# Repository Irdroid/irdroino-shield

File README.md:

# Irdroino-shield

Irdroino shield is a prototyping shield for Arduino Like boards such as Maple, Pinguino, Olimexino and Arduino

  - Stackable headers
- Two buttons
- One LED
- Prototype Area PTH 
- SMD IC Area
- IR Receiver IC (OSRB38C9BA)
- One Infrared LED (L-53F3BT)

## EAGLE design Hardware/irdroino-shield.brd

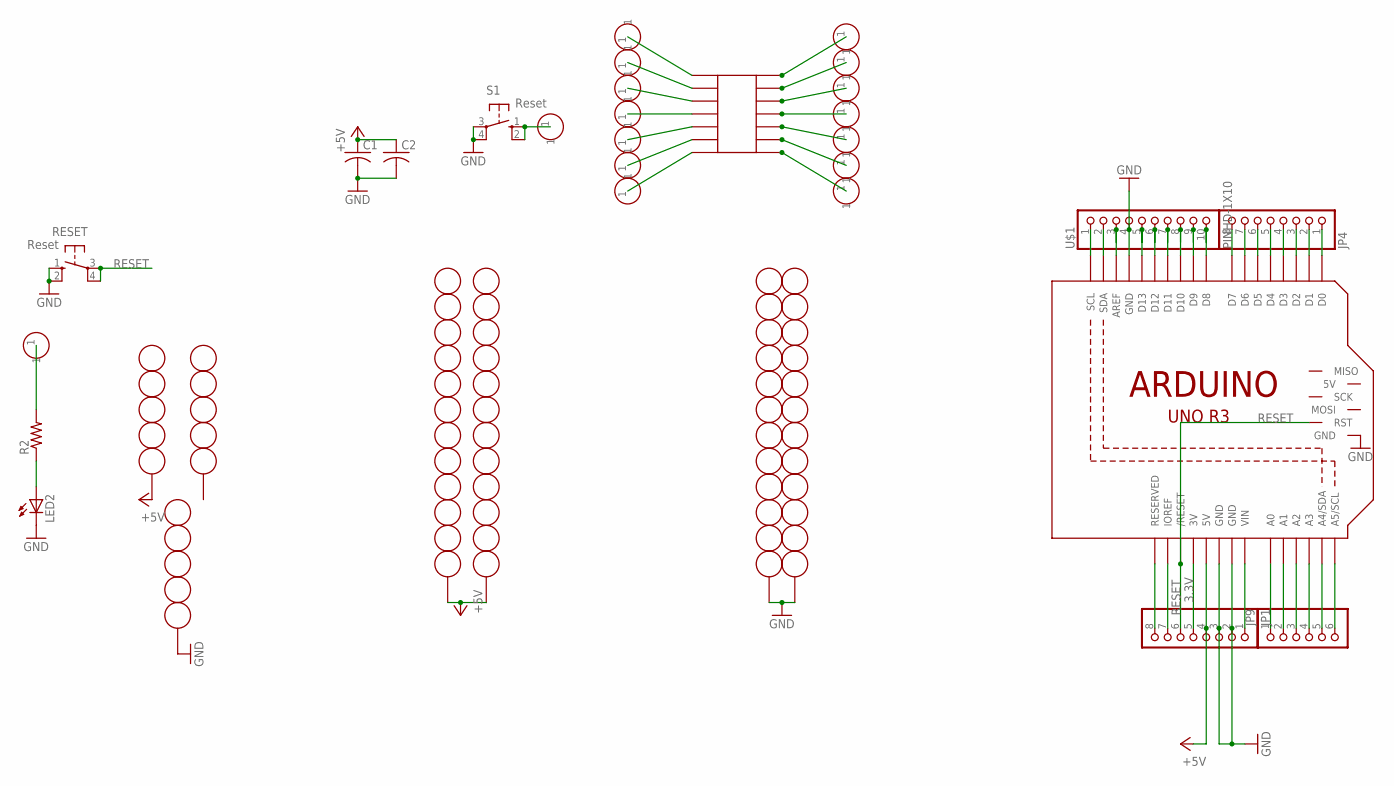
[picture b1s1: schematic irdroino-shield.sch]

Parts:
C1, C2: C-US025-025X050; C025-025X050
GNDSTRIP1, GNDSTRIP2: 12-STRIP
IC1: SMD-14; SO-14NMW
JP1, JP4: PINHD-1X8BIG; 1X08-BIG
JP9: PINHD-1X6B; 1X06-BIG
LED2: LED3MM
M1: ARDUINO_R3_ICSP; ARDUINOR3_ICSP
R2: R-US_0207/5V; 0207/5V
RESET: Reset; B3F-10XX
S1: Reset; B3F-10XX
U$1: PINHD-1X10; 1X10-BIG
U$2, U$4, U$6, U$8, U$9, U$16, U$19, U$25, U$27, U$34, U$35, U$37, U$38, U$39, U$40, U$41: PERFHOLE
U$3, U$24, U$43: 5-STRIP
VCCSTRIP1, VCCSTRIP2: 12-STRIP

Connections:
3.3V: JP1.5, M1.3V
+5V: C1.1, C2.1, JP1.4, M1.5V, U$24.P$3, VCCSTRIP1.P$1, VCCSTRIP2.P$1
GND: C1.2, C2.2, GNDSTRIP1.P$1, GNDSTRIP2.P$1, JP1.2, JP1.3, LED2.K (C), M1.GND, M1.GND@1 (GND), M1.GND@2 (GND), M1.GND@3 (GND), RESET.1 (S), RESET.2 (S1), S1.3, S1.4 (P1), U$1.4, U$43.P$3
unnamed: M1.AREF, U$1.3
unnamed: JP1.8, M1.RESERVED
unnamed: M1.D13, U$1.5
unnamed: JP1.7, M1.IOREF
unnamed: R2.2, U$4.1
unnamed: LED2.A, R2.1
unnamed: M1.D12, U$1.6
unnamed: M1.D11, U$1.7
unnamed: M1.D10, U$1.8
unnamed: M1.D9, U$1.9
unnamed: M1.D8, U$1.10
unnamed: JP9.1, M1.A0
unnamed: JP9.2, M1.A1
unnamed: JP9.3, M1.A2
unnamed: JP9.4, M1.A3
unnamed: JP9.5, M1.A4 (A4/SDA)
unnamed: JP9.6, M1.A5 (A5/SCL)
unnamed: JP4.1, M1.D0
unnamed: JP4.2, M1.D1
unnamed: JP4.3, M1.D2
unnamed: JP4.4, M1.D3
unnamed: JP4.5, M1.D4
unnamed: IC1.P$1, U$2.1
unnamed: IC1.P$2, U$6.1
unnamed: JP4.6, M1.D5
unnamed: JP4.7, M1.D6
unnamed: IC1.P$3, U$8.1
unnamed: IC1.P$4, U$9.1
unnamed: IC1.P$5, U$19.1
unnamed: JP4.8, M1.D7
unnamed: JP1.1, M1.VIN
unnamed: M1.SCL, U$1.1
unnamed: IC1.P$6, U$25.1
unnamed: IC1.P$7, U$27.1
unnamed: IC1.P$8, U$34.1
unnamed: IC1.P$9, U$35.1
unnamed: IC1.P$10, U$37.1
unnamed: M1.SDA, U$1.2
unnamed: IC1.P$11, U$38.1
unnamed: IC1.P$12, U$39.1
unnamed: IC1.P$13, U$40.1
unnamed: IC1.P$14, U$41.1
unnamed: S1.1 (S), S1.2 (S1), U$16.1
RESET: JP1.6, M1.RESET (/RESET), M1.RESET_ICSP (RST), RESET.3, RESET.4 (P1)

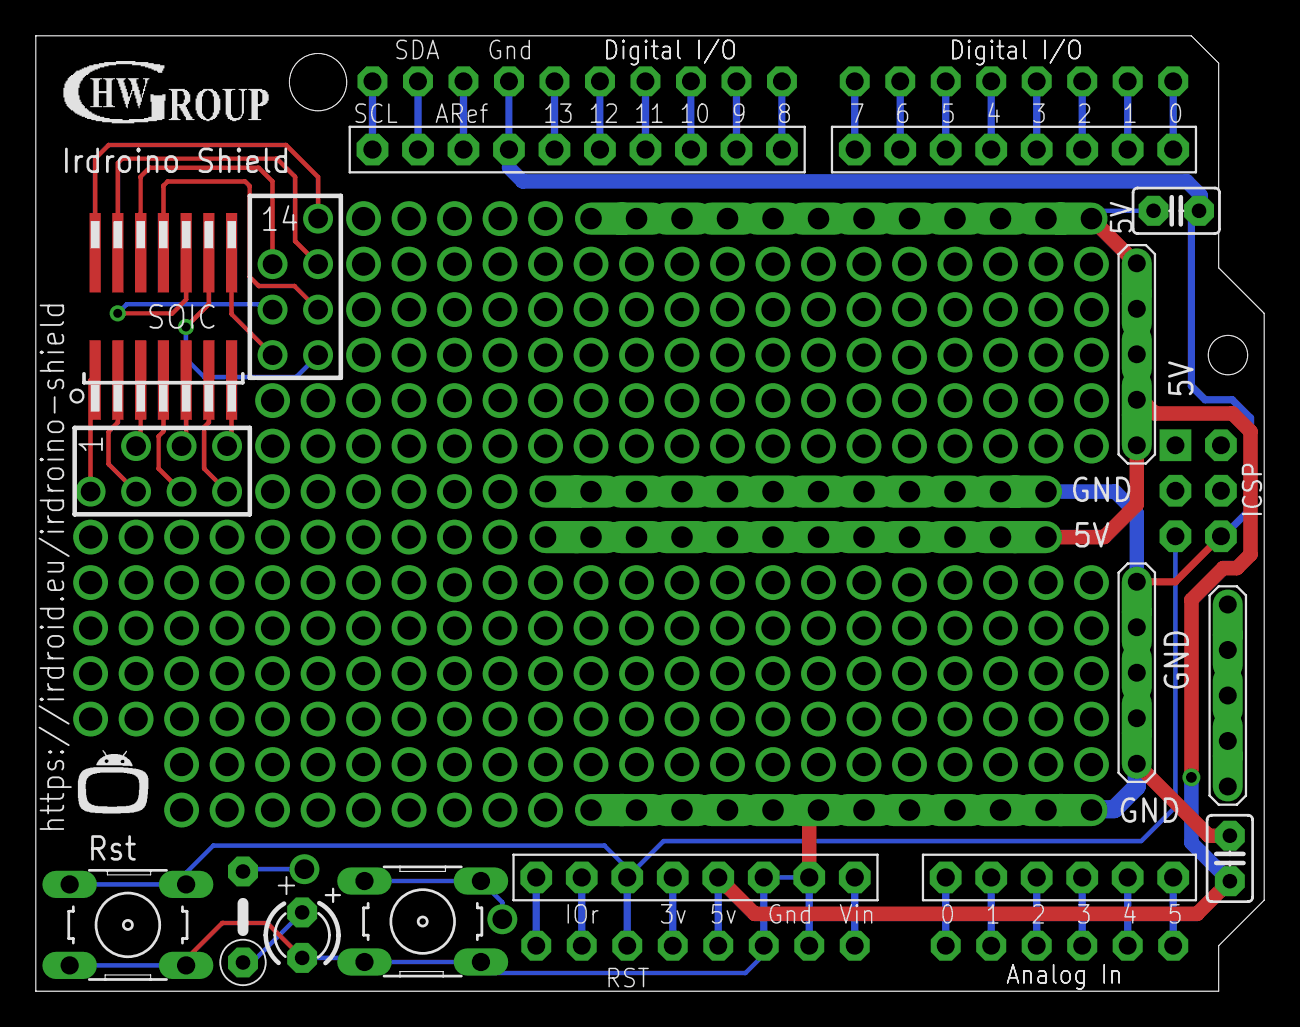
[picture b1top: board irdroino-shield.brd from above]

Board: 2 copper layers, 68.6 x 53.3 mm, 38 parts (1 on the bottom side), 47 nets.

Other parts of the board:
U$5: HWGROUP
U$36: ADAFRUIT_9MM
U$44: IRDROIDLOGO

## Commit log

2018-03-07 Initial commit
    Initial commit
2018-03-07 second commit
    Updated schematic and provided schematic in PDF.
2018-03-07 Removed temp files
    temp files removed
2019-03-13 Added demo code for Irdroino
    Added demo code for Irdroino
2019-03-13 Changed name
    Changed name

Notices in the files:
parts and their libraries:
microbuilder: This work is placed in the public domain, and may be freely used for commercial and non-commercial work with the following conditions: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
